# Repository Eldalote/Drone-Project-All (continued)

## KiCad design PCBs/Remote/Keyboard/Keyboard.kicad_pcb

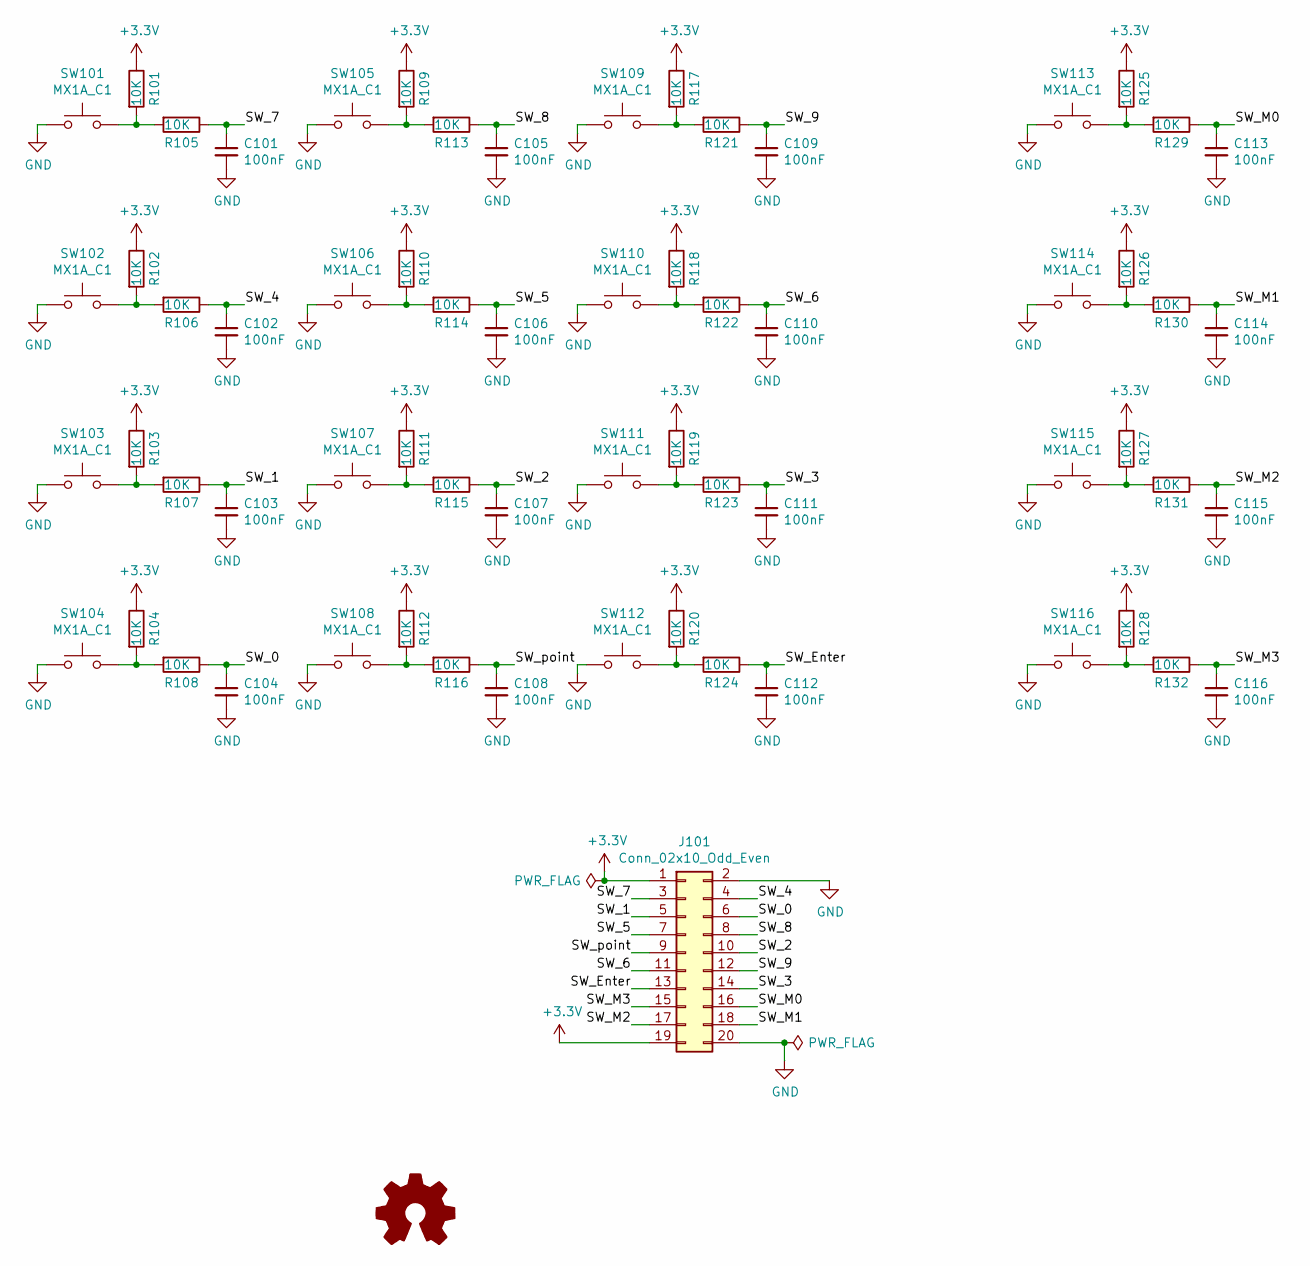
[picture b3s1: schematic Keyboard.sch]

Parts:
C101, C102, C103, C104, C105, C106, C107, C108, C109, C110, C111, C112, C113, C114, C115, C116: 100nF; C_0805_2012Metric_Pad1.15x1.40mm_HandSolder; LCSC C49678
J101: Conn_02x10_Odd_Even; PinHeader_2x10_P2.54mm_Vertical
LOGO101: Logo_Open_Hardware_Small; OSHW-Logo_5.7x6mm_SilkScreen
R101, R102, R103, R104, R105, R106, R107, R108, R109, R110, R111, R112, R113, R114, R115, R116, R117, R118, R119, R120, R121, R122, R123, R124, R125, R126, R127, R128, R129, R130, R131, R132: 10K; R_0805_2012Metric_Pad1.15x1.40mm_HandSolder; LCSC C17414
SW101, SW102, SW103, SW104, SW105, SW106, SW107, SW108, SW109, SW110, SW111, SW112, SW113, SW114, SW115, SW116: MX1A_C1; SW_Cherry_MX_1.00u_PCB; DigiKey CH310-ND

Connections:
+3V3: J101.1, J101.19, R101.1, R102.1, R103.1, R104.1, R109.1, R110.1, R111.1, R112.1, R117.1, R118.1, R119.1, R120.1, R125.1, R126.1, R127.1, R128.1
/SW_0: C104.1, J101.6, R108.1
/SW_1: C103.1, J101.5, R107.1
/SW_2: C107.1, J101.10, R115.1
/SW_3: C111.1, J101.14, R123.1
/SW_4: C102.1, J101.4, R106.1
/SW_5: C106.1, J101.7, R114.1
/SW_6: C110.1, J101.11, R122.1
/SW_7: C101.1, J101.3, R105.1
/SW_8: C105.1, J101.8, R113.1
/SW_9: C109.1, J101.12, R121.1
/SW_Enter: C112.1, J101.13, R124.1
/SW_M0: C113.1, J101.16, R129.1
/SW_M1: C114.1, J101.18, R130.1
/SW_M2: C115.1, J101.17, R131.1
/SW_M3: C116.1, J101.15, R132.1
/SW_point: C108.1, J101.9, R116.1
GND: C101.2, C102.2, C103.2, C104.2, C105.2, C106.2, C107.2, C108.2, C109.2, C110.2, C111.2, C112.2, C113.2, C114.2, C115.2, C116.2, J101.2, J101.20, SW101.1, SW102.1, SW103.1, SW104.1, SW105.1, SW106.1, SW107.1, SW108.1, SW109.1, SW110.1, SW111.1, SW112.1, SW113.1, SW114.1, SW115.1, SW116.1
unnamed: R101.2, R105.2, SW101.2
unnamed: R102.2, R106.2, SW102.2
unnamed: R103.2, R107.2, SW103.2
unnamed: R104.2, R108.2, SW104.2
unnamed: R109.2, R113.2, SW105.2
unnamed: R110.2, R114.2, SW106.2
unnamed: R111.2, R115.2, SW107.2
unnamed: R112.2, R116.2, SW108.2
unnamed: R117.2, R121.2, SW109.2
unnamed: R118.2, R122.2, SW110.2
unnamed: R119.2, R123.2, SW111.2
unnamed: R120.2, R124.2, SW112.2
unnamed: R125.2, R129.2, SW113.2
unnamed: R126.2, R130.2, SW114.2
unnamed: R127.2, R131.2, SW115.2
unnamed: R128.2, R132.2, SW116.2

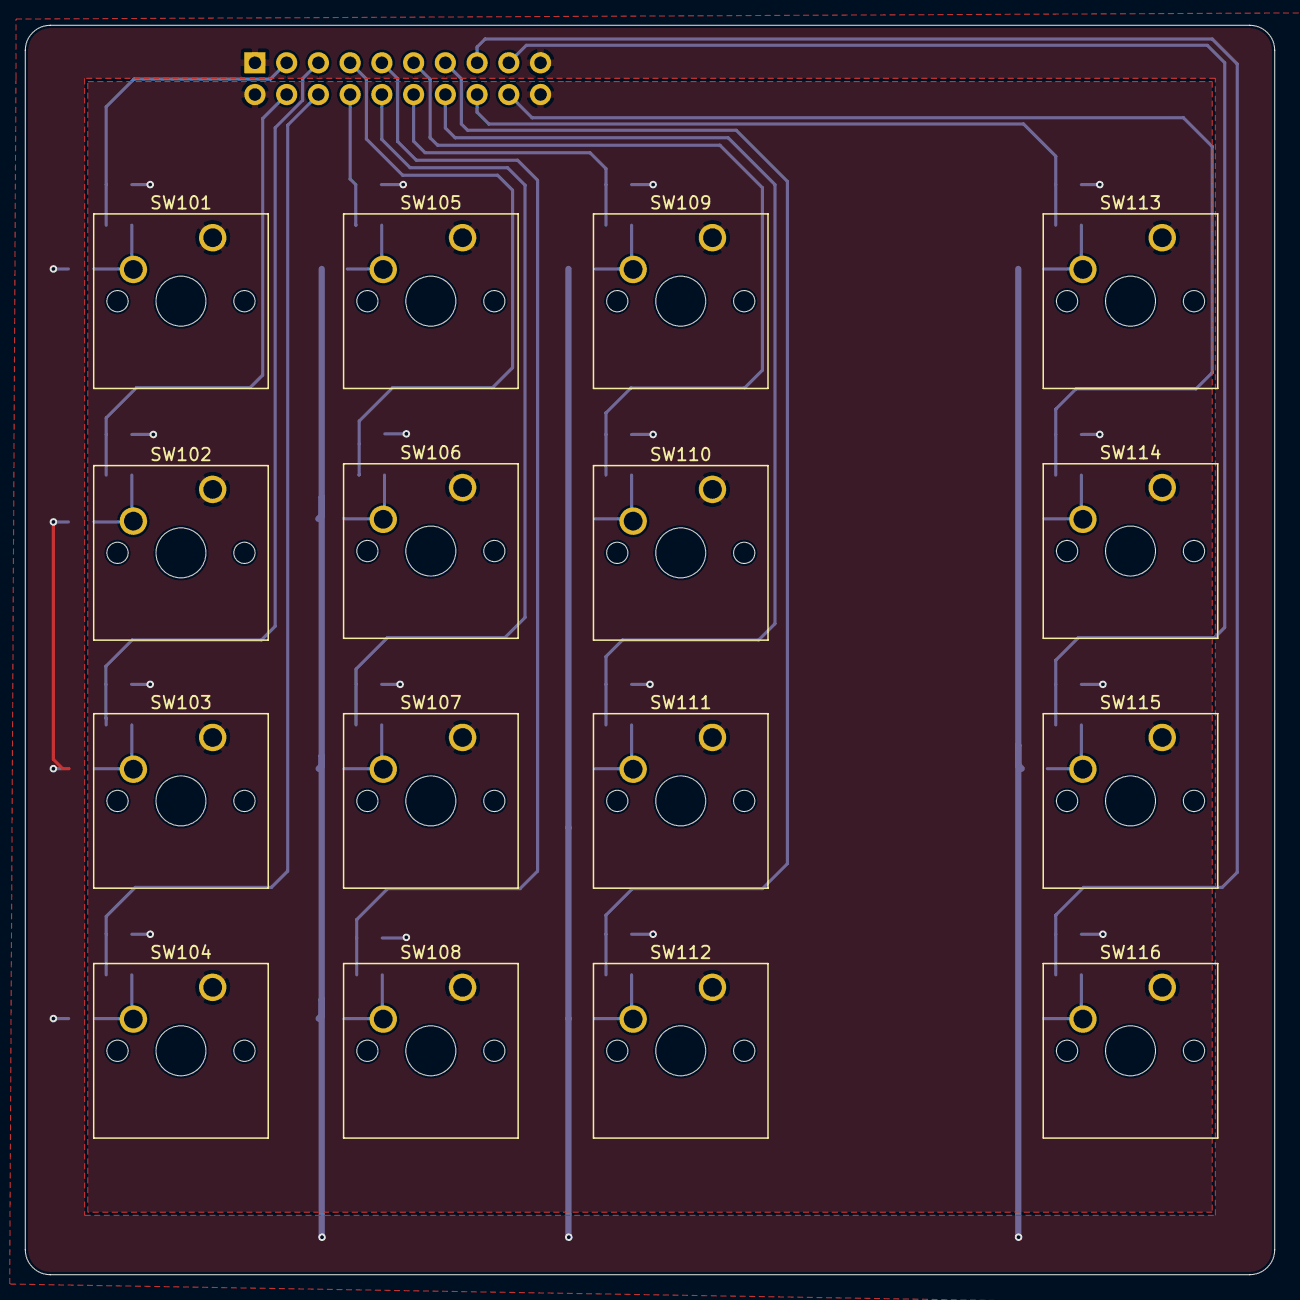
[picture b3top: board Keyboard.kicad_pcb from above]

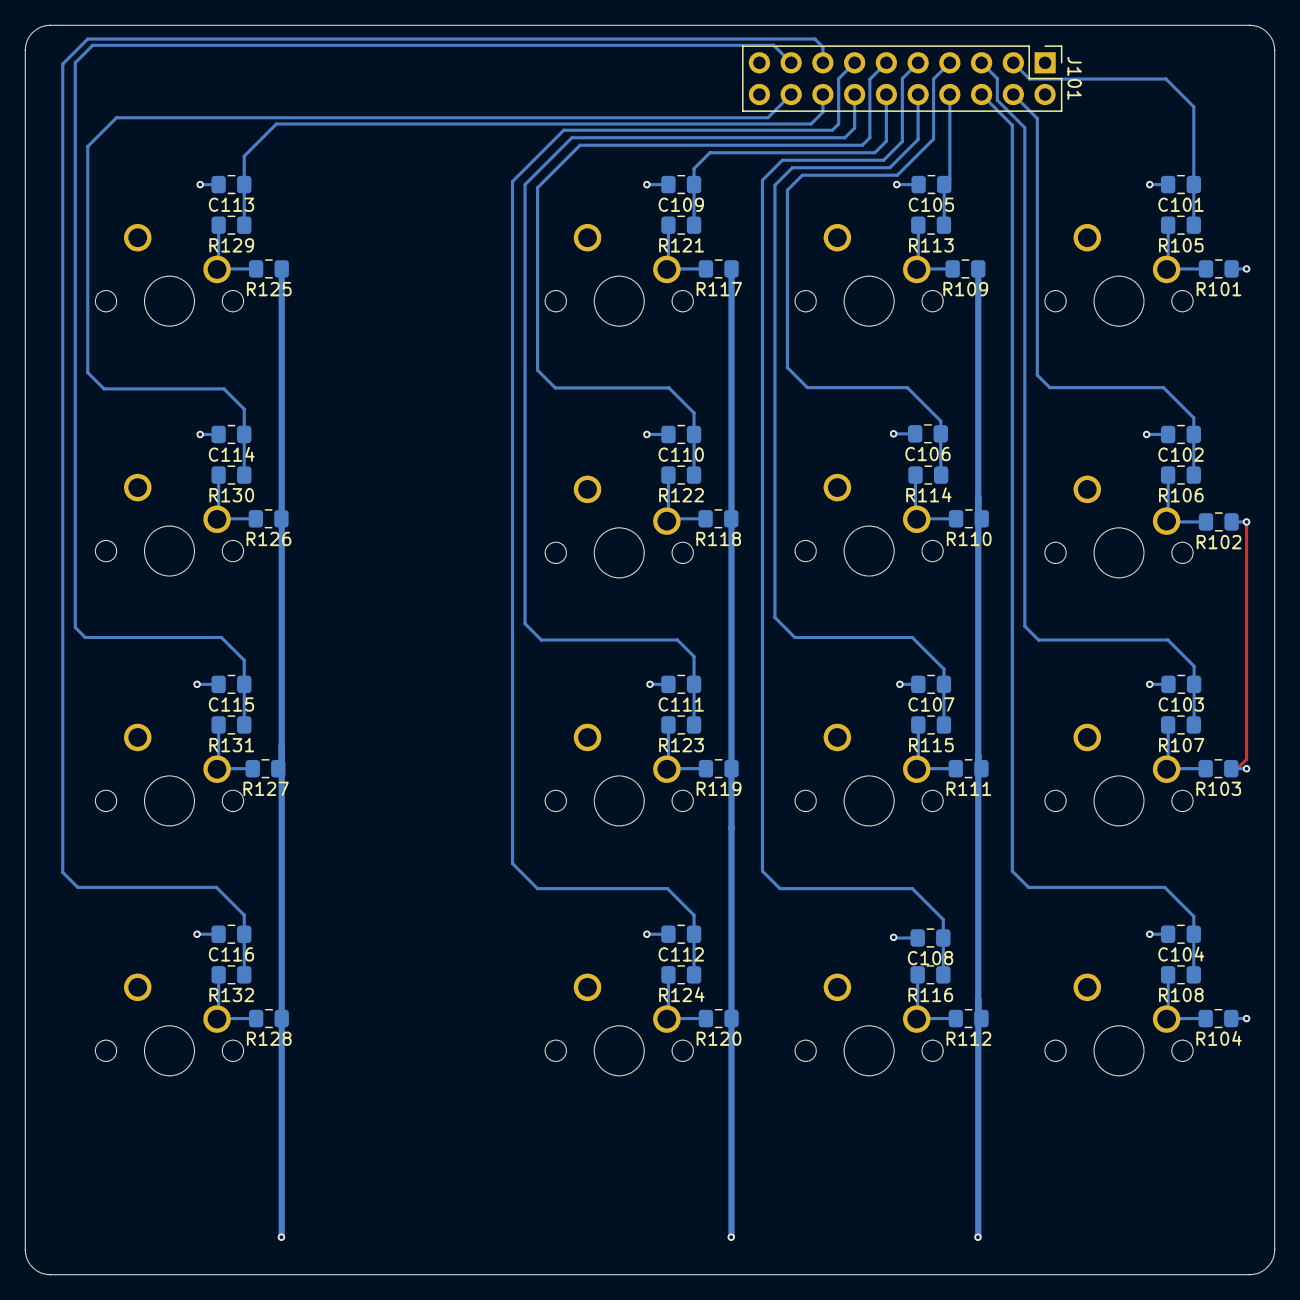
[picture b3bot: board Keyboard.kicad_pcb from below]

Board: 2 copper layers, 100.0 x 100.0 mm, 66 parts (49 on the bottom side), 34 nets.

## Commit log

2020-11-02 First commit, with some datasheets and a start of the remote PCB
2020-11-06 Bezig met LEDS
2020-11-16 Continued work with the center board
2020-11-18 Note: Schmitt trigger for joystick Buttons TODO
2020-11-20 Made the keyboard PCB. With LPC software started pin assignment on the LPC
2020-12-09 Screen POT->PWM and RGB LEDS reworked, making space on the CPU pins. Almost done
2020-12-11 Finished leds, redid a lot of PCB wiring. Almost done there now.
2020-12-14 Centerboard v0.1 is done.
2020-12-14 More finishing work on remote-centerboard. Copied in the Drone main board, did some cleaning up on that. Started work on more neat and clean lessons learned documents
2020-12-18 Redid the radio PCB layout on both drone and remote PCB. Drone PCB had old schematic, remote PCB layout wasn't ideal.
    Copied in the VHDL project files from the seperate VHDL project into the main "All in one" project.
2020-12-18 Tiny readme update
2020-12-18 End of day commit (just lessons learned)
2020-12-21 Some cleanup, and PCB antenna removal.
    Last edits before asking for reddit feedback.
2020-12-24 Minor tweaks. Improved groundplane around FPGA core (removed and relocated a few power vias) and flipped clock circuit to the same side as the FPGA.
2021-01-15 Added PDFs of schematics. Corrected a few value labels in drone schematic.
2021-02-22 Did a little research, made note to myself.
2021-03-01 Started to recheck components, and make a better BOM.
2021-03-09 Lots of work to check every component, add Manufacturers number (instead of LCSC or digikey and mouser numbers)
    Changed to USB-C connector, almost done with that sheet. Components checked, need to redo Sheet IO
2021-03-16 Reworking and checking up to sensors page on main board. Added some datasheets to project
2021-03-18 Finished (?) the schematic check and update. Next: PCB update
2021-03-18 Minor PCB work
2021-03-23 Finished redoing PCB.
2021-03-23 On hold update
